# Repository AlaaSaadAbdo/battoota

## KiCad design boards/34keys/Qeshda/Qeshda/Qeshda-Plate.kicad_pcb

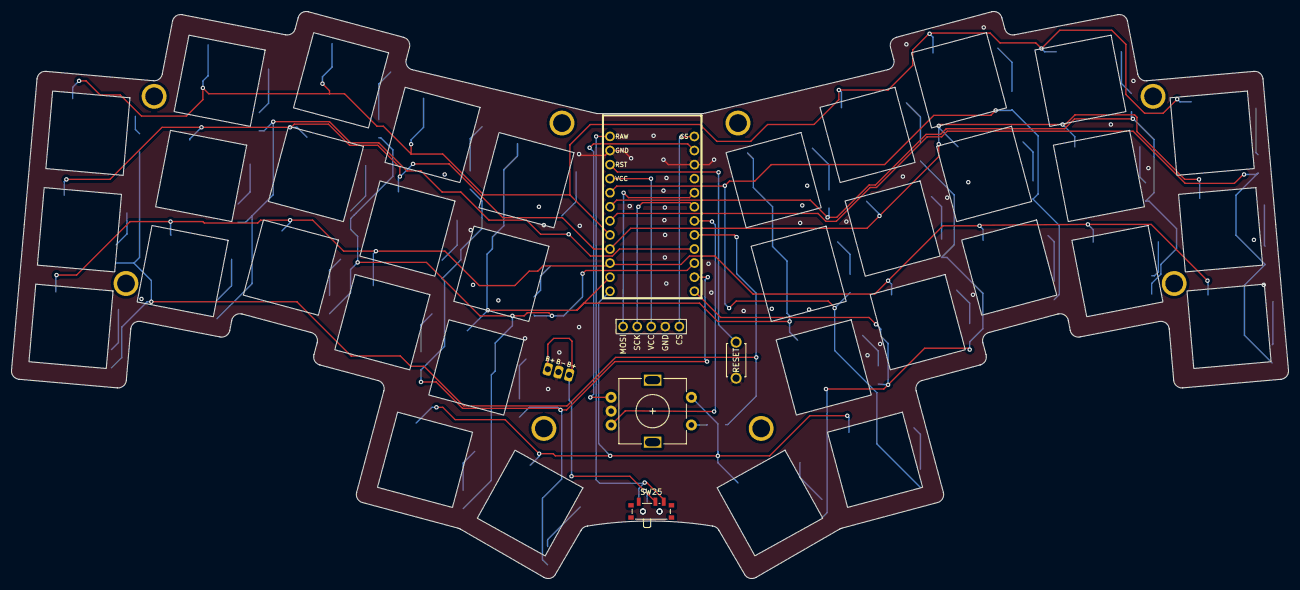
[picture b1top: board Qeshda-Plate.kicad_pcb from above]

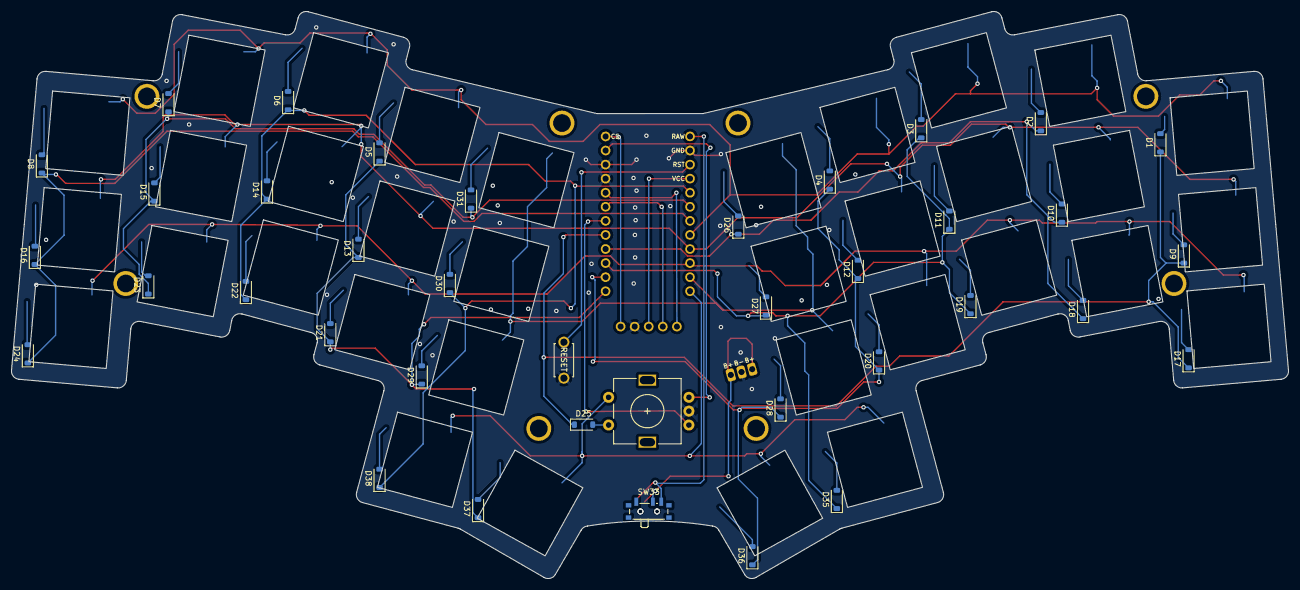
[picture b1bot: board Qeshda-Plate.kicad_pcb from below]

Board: 2 copper layers, 230.5 x 102.4 mm, 76 parts (37 on the bottom side), 20 nets.

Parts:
D1, D2, D3, D4, D5, D6, D7, D8, D9, D10, D11, D12, D13, D14, D15, D16, D17, D18, D19, D20, D21, D22, D23, D24, D25, D26, D27, D28, D29, D30, D31, D35, D36, D37, D38: 1N4148; D_SOD-123
Display1: nice!view; nice_view
J1: Conn_01x08_Female; 3JST_BAT
SW1, SW2, SW3, SW4, SW5, SW6, SW7, SW8, SW9, SW10, SW11, SW12, SW13, SW14, SW15, SW16, SW17, SW18, SW19, SW20, SW21, SW22, SW23, SW24, SW27, SW28, SW29, SW30, SW31, SW32, SW37, SW38, SW39, SW40: SW_Push; empty20x20
SW25, SW33: SW_SPDT; SW_SPDT_PCM12
SW26: Rotary_Encoder_Switch; RotaryEncoder_Alps_EC11E-Switch_Vertical_H20mm-keebio_modif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
SW34: SW_Push; ResetSW
U1: nice_nano

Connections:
3V3: Display1.3 (VCC), U1.21 (VCC)
EncL: SW26.A, U1.2 (RX1/P0.08)
EncR: SW26.B, U1.7 (P0.22)
GND: Display1.4 (GND), J1.2, SW26.C, SW34.2, U1.3 (GND), U1.4 (GND), U1.23 (GND)
MOSI: Display1.1 (MOSI), U1.5 (P0.17)
NVCS: Display1.5 (CS), U1.1 (TX0/P0.06)
unnamed: D25.2 (A), SW26.S1
RAW: SW25.3 (C), SW33.3 (C), U1.24 (BATIN/P0.04)
RESET: SW34.1, U1.22 (RST)
SCK: Display1.2 (SCK), U1.6 (P0.20)
bat+: J1.1, J1.3, SW25.2 (B), SW33.2 (B)
col_0: D1.1 (K), D9.1 (K), D17.1 (K), D25.1 (K), U1.8 (P0.24)
col_1: D2.1 (K), D10.1 (K), D18.1 (K), D26.1 (K), U1.9 (P1.00)
col_2: D3.1 (K), D11.1 (K), D19.1 (K), D27.1 (K), D35.1 (K), U1.10 (P0.11)
col_3: D4.1 (K), D12.1 (K), D20.1 (K), D28.1 (K), D36.1 (K), U1.11 (P1.04)
col_4: D5.1 (K), D13.1 (K), D21.1 (K), D29.1 (K), D37.1 (K), U1.12 (P1.06)
col_5: D6.1 (K), D14.1 (K), D22.1 (K), D30.1 (K), D38.1 (K), U1.20 (AIN7/P0.31)
col_6: D7.1 (K), D15.1 (K), D23.1 (K), D31.1 (K), U1.19 (AIN5/P0.29)
col_7: D8.1 (K), D16.1 (K), D24.1 (K), U1.18 (AIN0/P0.02)
row_4: SW26.S2, U1.13 (NFC1/P0.09)

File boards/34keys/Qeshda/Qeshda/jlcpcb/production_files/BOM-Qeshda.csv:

Comment,Designator,Footprint,LCSC
1N4148,"D1,D10,D11,D12,D13,D14,D15,D16,D17,D18,D19,D2,D20,D21,D22,D23,D24,D25,D26,D27,D28,D29,D3,D30,D31,D35,D36,D37,D38,D4,D5,D6,D7,D8,D9",D_SOD-123,C909967
Conn_01x08_Female,J1,3JST_BAT,
nice_nano,U1,nice_nano,
SW_Push,SW21,choc_hotswap,
SW_Push,SW30,choc_hotswap,
SW_Push,SW22,choc_hotswap,
Rotary_Encoder_Switch,SW26,RotaryEncoder_Alps_EC11E-Switch_Vertical_H20mm-keebio_modified,
SW_Push,SW34,ResetSW,
SW_Push,SW40,choc_hotswap,
SW_Push,SW39,choc_hotswap,
SW_Push,SW38,choc_hotswap,
SW_Push,SW37,choc_hotswap,
SW_Push,SW32,choc_hotswap,
SW_Push,SW31,choc_hotswap,
SW_Push,SW29,choc_hotswap,
SW_Push,SW28,choc_hotswap,
SW_Push,SW27,choc_hotswap,
SW_SPDT,SW25,SW_SPDT_PCM12,
SW_Push,SW24,choc_hotswap,
SW_Push,SW23,choc_hotswap,
SW_Push,SW20,choc_hotswap,
SW_Push,SW19,choc_hotswap,
SW_Push,SW18,choc_hotswap,
SW_Push,SW17,choc_hotswap,
SW_Push,SW16,choc_hotswap,
SW_Push,SW15,choc_hotswap,
SW_Push,SW14,choc_hotswap,
SW_Push,SW13,choc_hotswap,
SW_Push,SW12,choc_hotswap,
SW_Push,SW11,choc_hotswap,
SW_Push,SW10,choc_hotswap,
SW_Push,SW9,choc_hotswap,
SW_Push,SW8,choc_hotswap,
SW_Push,SW7,choc_hotswap,
SW_Push,SW6,choc_hotswap,
SW_Push,SW5,choc_hotswap,
SW_Push,SW4,choc_hotswap,
SW_Push,SW3,choc_hotswap,
SW_Push,SW2,choc_hotswap,
SW_Push,SW1,choc_hotswap,
nice!view,Display1,nice_view,
SW_SPDT,SW33,SW_SPDT_PCM12,

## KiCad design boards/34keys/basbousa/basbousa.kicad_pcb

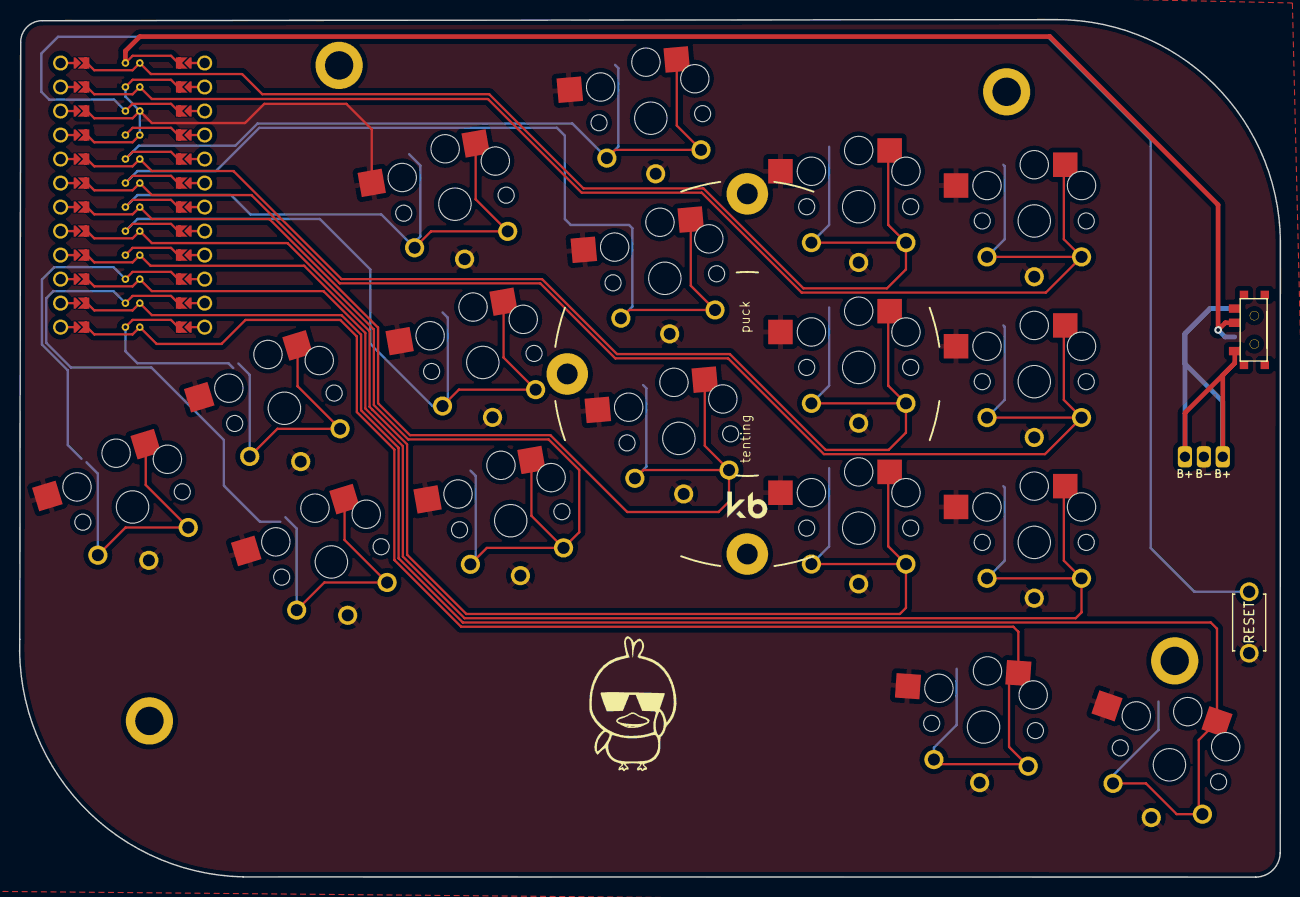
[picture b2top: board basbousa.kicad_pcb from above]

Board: 2 copper layers, 133.4 x 90.7 mm, 21 parts (0 on the bottom side), 3 nets.

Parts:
B1: ResetSW
PAD1: bat
S1, S3, S5, S7, S9, S11, S13, S15, S17, S19, S21, S23, S25, S27, S29, S31, S33: key
T1, T2: SPDT_C128955

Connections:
Braw: PAD1.1, T1.1, T2.1
GND: B1.2, PAD1.2, S1.2, S3.2, S5.2, S7.2, S9.2, S11.2, S13.2, S15.2, S17.2, S19.2, S21.2, S23.2, S25.2, S27.2, S29.2, S31.2, S33.2
RAW: T1.2, T2.2

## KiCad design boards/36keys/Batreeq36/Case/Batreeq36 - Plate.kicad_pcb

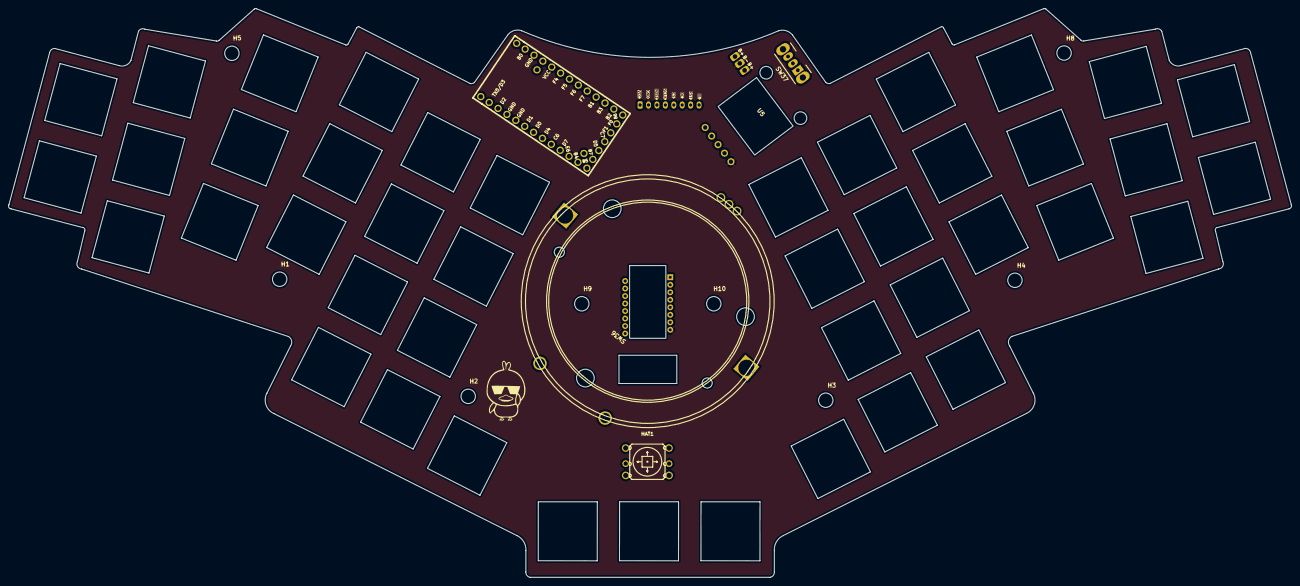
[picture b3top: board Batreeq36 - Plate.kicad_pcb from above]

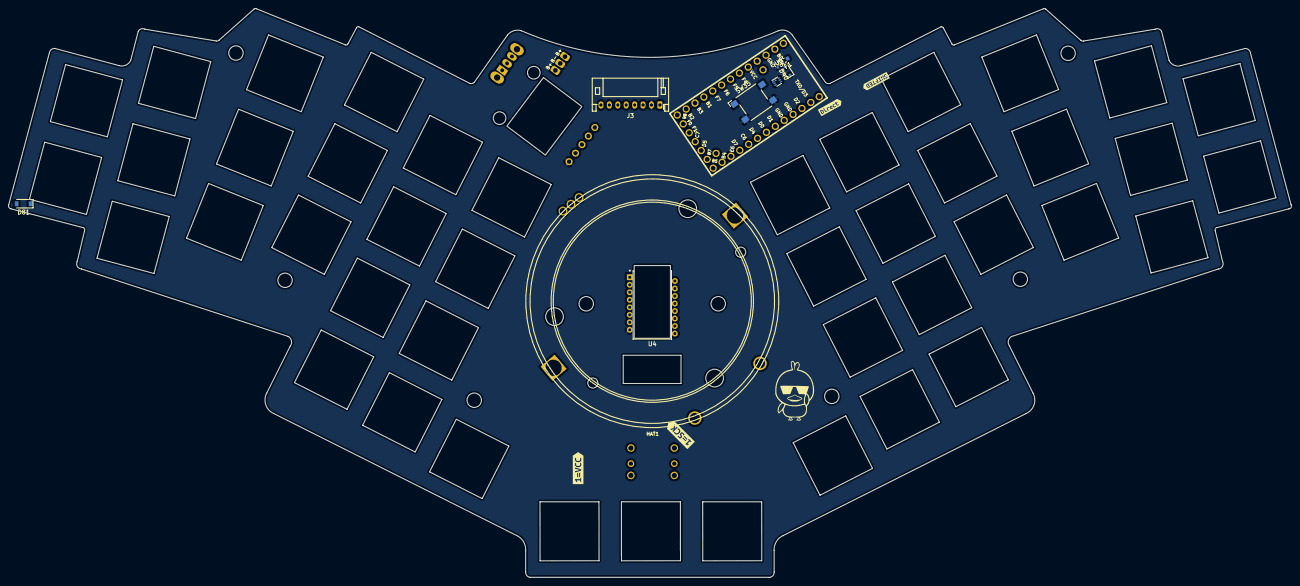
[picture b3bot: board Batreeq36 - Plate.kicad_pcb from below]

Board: 2 copper layers, 304.4 x 135.0 mm, 78 parts (12 on the bottom side), 21 nets, no tracks yet.

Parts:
C6: 4u7; C_0402_1005Metric
D40: B5817WS; D_SOD-323
D41, D42, D44, D45, D46, D47, D48, D49, D50, D51, D52, D53, D54, D55, D56, D57, D58, D59, D60, D61, D62, D63, D64, D65, D66, D67, D68, D69, D70, D71, D72, D73, D74, D83, D84, D85, D86, D87, D88, D89, D90, D91, D92: SK6812MINI-E; 14mm-switch-hole
D81: 1N4148; D_SOD-123
F1: 500mA; Fuse_0603_1608Metric
G1: LOGO
H1, H2, H3, H4, H5, H8, H9, H10: MountingHole_Pad; MountingHole_M3-edgeCut
HAT1: 5Way-Tactile_K1-1506DN-01; 5Way-non-reverse
J3: Conn_01x08_Female; JST_PH_S8B-PH-K_1x08_P2.00mm_Horizontal
J4: Conn_01x08_Female; 3JST_BAT
SW35: SW_Push; SW_SPST_Omron_B3FS-100xP
SW36: RotaryEncoder; PERS56v2
SW37: SW_SPDT; SW_CuK_OS102011MA1QN1_SPDT_Angled
U1: Elite-C; Helios-SeaPicro
U4: PMW3360DM-T2QU
U5: DRV2605L; Pimoroni Haptic Buzz DRV2605L Driver
U6: 74LVC1T45; SOT-563
kibuzzard-63B827BA: G***; kibuzzard-63B827BA
kibuzzard-63B8279E: G***; kibuzzard-63B8279E
kibuzzard-638CDE9C: G***; kibuzzard-638CDE9C
kibuzzard-638CDF14: G***; kibuzzard-638CDF14
kibuzzard-639A2BF5: G***; kibuzzard-639A2BF5
kibuzzard-639A2C9D: G***; kibuzzard-639A2C9D
kibuzzard-639A2C18: G***; kibuzzard-639A2C18
kibuzzard-639A2C87: G***; kibuzzard-639A2C87
kibuzzard-639A2C93: G***; kibuzzard-639A2C93
kibuzzard-639A2CA8: G***; kibuzzard-639A2CA8
kibuzzard-639A2CB2: G***; kibuzzard-639A2CB2
kibuzzard-639A2CBD: G***; kibuzzard-639A2CBD

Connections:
EncL: SW36.A, U1.20 (A3/PF4)
EncR: SW36.B, U1.19 (A2/PF5)
GND: C6.2, J3.2, J4.2, SW35.2, SW36.C, U1.3 (GND), U1.4 (GND), U1.23 (GND), U4.8 (GND), U5.5 (GND), U6.2 (GND)
LED_3V3: U1.18 (A1/PF6), U6.3 (A)
MISO: U1.15 (14/PB3), U4.12 (MISO)
MOSI: J3.3, U1.14 (16/PB2), U4.11 (MOSI)
MOTION: U1.1 (TX0/PD3), U4.9 (MOTION)
NCS: U1.2 (RX1/PD2), U4.13 (~NCS)
unnamed: D40.2 (A), F1.1
RAW: C6.1, F1.2, SW37.3 (C), U1.24 (B0), U6.6 (VCCB)
RESET: SW35.1, U1.22 (RST)
SCL: U1.6 (3/PD0), U5.3 (SCL)
SCLK: J3.4, U1.16 (15/PB1), U4.10 (SCLK)
SDA: U1.5 (2/PD1), U5.2 (SDA)
TFT_BL: J3.8, U1.26 (D5)
TFT_CS: J3.5, U1.17 (A0/PF7)
TFT_DC: J3.6, U1.27 (C7)
TFT_RST: J3.7, U1.25 (B7)
VCC: J3.1, U1.21 (VCC), U4.5 (VDDIO), U5.1 (VDD), U6.1 (VCCA), U6.5 (DIR)
bat+: J4.1, J4.3, SW37.2 (B)
row_5: HAT1.4, U1.13 (10/PB6)

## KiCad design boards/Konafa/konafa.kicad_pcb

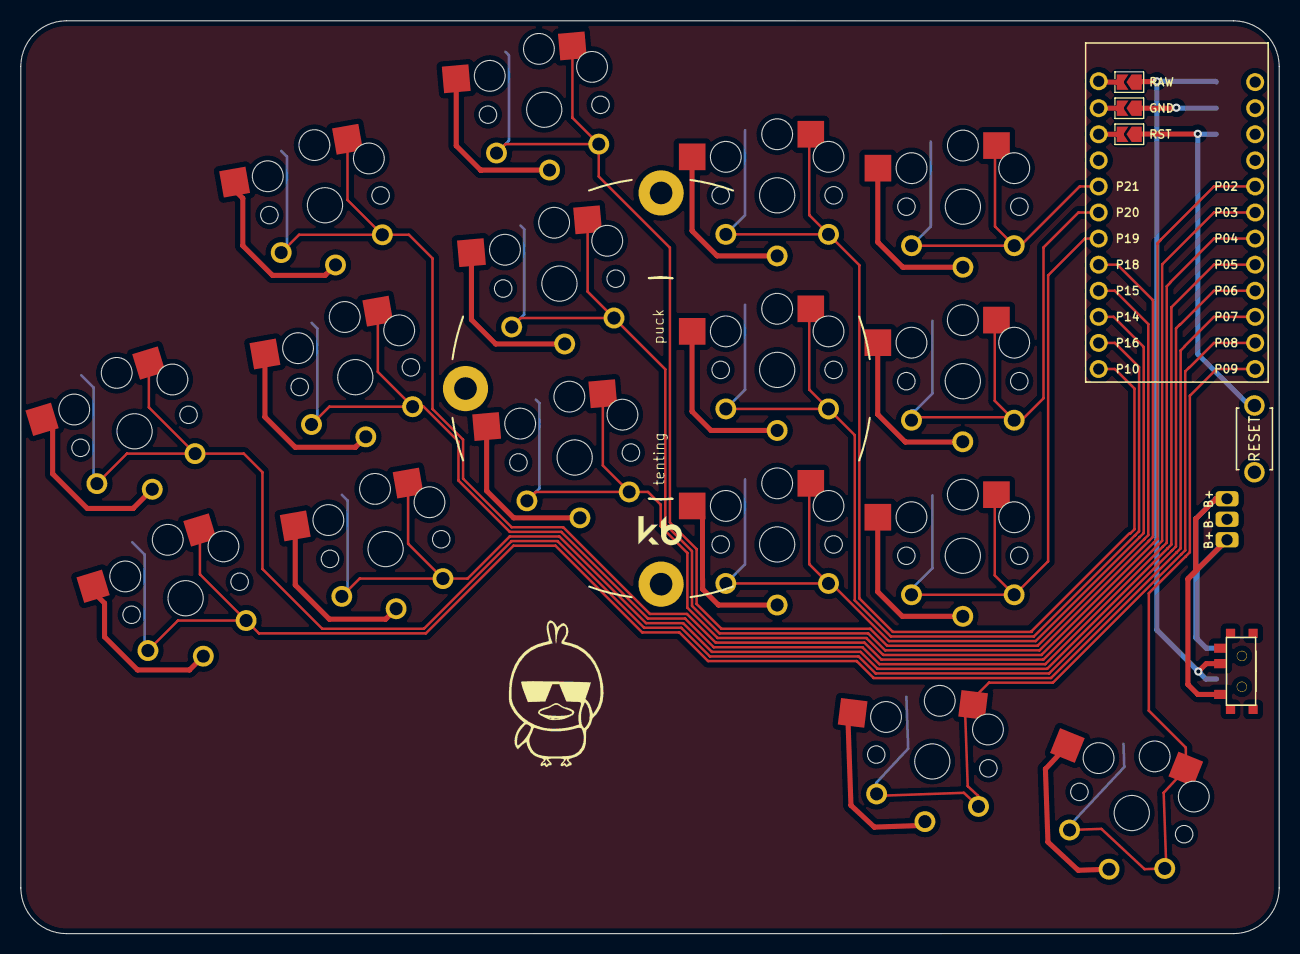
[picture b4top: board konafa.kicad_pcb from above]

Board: 2 copper layers, 122.6 x 88.9 mm, 21 parts (0 on the bottom side), 20 nets.

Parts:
B1: ResetSW
MCU1: ProMicro
PAD1: bat
S3, S5, S7, S9, S11, S13, S15, S17, S19, S21, S23, S23#2, S27, S29, S31, S33: choc_hotswap_key
T1, T2: SPDT_C128955

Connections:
Braw: PAD1.1, PAD1.3, T1.1, T2.1
GND: B1.2, MCU1.2, PAD1.2, S3.2, S5.2, S7.2, S9.2, S11.2, S13.2, S15.2, S17.2, S19.2, S21.2, S23.2, S23#2.2, S27.2, S29.2, S31.2, S33.2
P2: MCU1.17, S13.1
P3: MCU1.18, S11.1
P4: MCU1.19, S9.1
P5: MCU1.20, S7.1
P6: MCU1.21, S5.1
P7: MCU1.22, S3.1
P8: MCU1.23, S31.1
P9: MCU1.24, S33.1
P10: MCU1.12, S23#2.1
P14: MCU1.10, S19.1
P15: MCU1.9, S17.1
P16: MCU1.11, S21.1
P18: MCU1.8, S15.1
P19: MCU1.7, S27.1
P20: MCU1.6, S29.1
P21: MCU1.5, S23.1
RAW: MCU1.1, T1.2, T2.2
RST: B1.1, MCU1.3
